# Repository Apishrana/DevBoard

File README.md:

# ATmega328 USB-C Devboard

Custom ATmega328-P based devboard for Arduino-like systems.

## Images

### Front

### Back

### PCB

### Schematic

---

## Features

- ATmega328-P as Microcontroller
- USB-C Support
- CH340G for USB-to-Serial
- Digital Pin `0-13`
- Analog Pin `A0-A5`
- 5 V VIN Regulation with L7805
- Reset Button

---

## Repository Structure

```text
.
├── BOM.csv
├── Devboard.kicad_pcb
├── Devboard.kicad_prl
├── Devboard.kicad_pro
├── Devboard.kicad_sch
├── grbr
│   ├── Devboard-B_Cu.gbl
│   ├── Devboard-B_Mask.gbs
│   ├── Devboard-B_Paste.gbp
│   ├── Devboard-B_Silkscreen.gbo
│   ├── Devboard-Edge_Cuts.gm1
│   ├── Devboard-F_Cu.gtl
│   ├── Devboard-F_Mask.gts
│   ├── Devboard-F_Paste.gtp
│   ├── Devboard-F_Silkscreen.gto
│   ├── Devboard-job.gbrjob
│   ├── Devboard-NPTH.drl
│   ├── Devboard-PTH.drl
│   └── Devboard.zip
├── image
│   ├── back.png
│   ├── front.png
│   ├── pcb.png
│   └── schema.png
└── README.md

3 directories, 23 files
```

---

## Board Details

- Microcontroller: `ATmega328-P`
- USB Serial: `CH340G`
- Main Clock: `16 MHz`
- USB Serial Clock: `12 MHz`
- Input Power: USB-C or `VIN`

`VIN`: `7-12 V`

---

## Author

Created by [Apish Rana](https://github.com/Apishrana)

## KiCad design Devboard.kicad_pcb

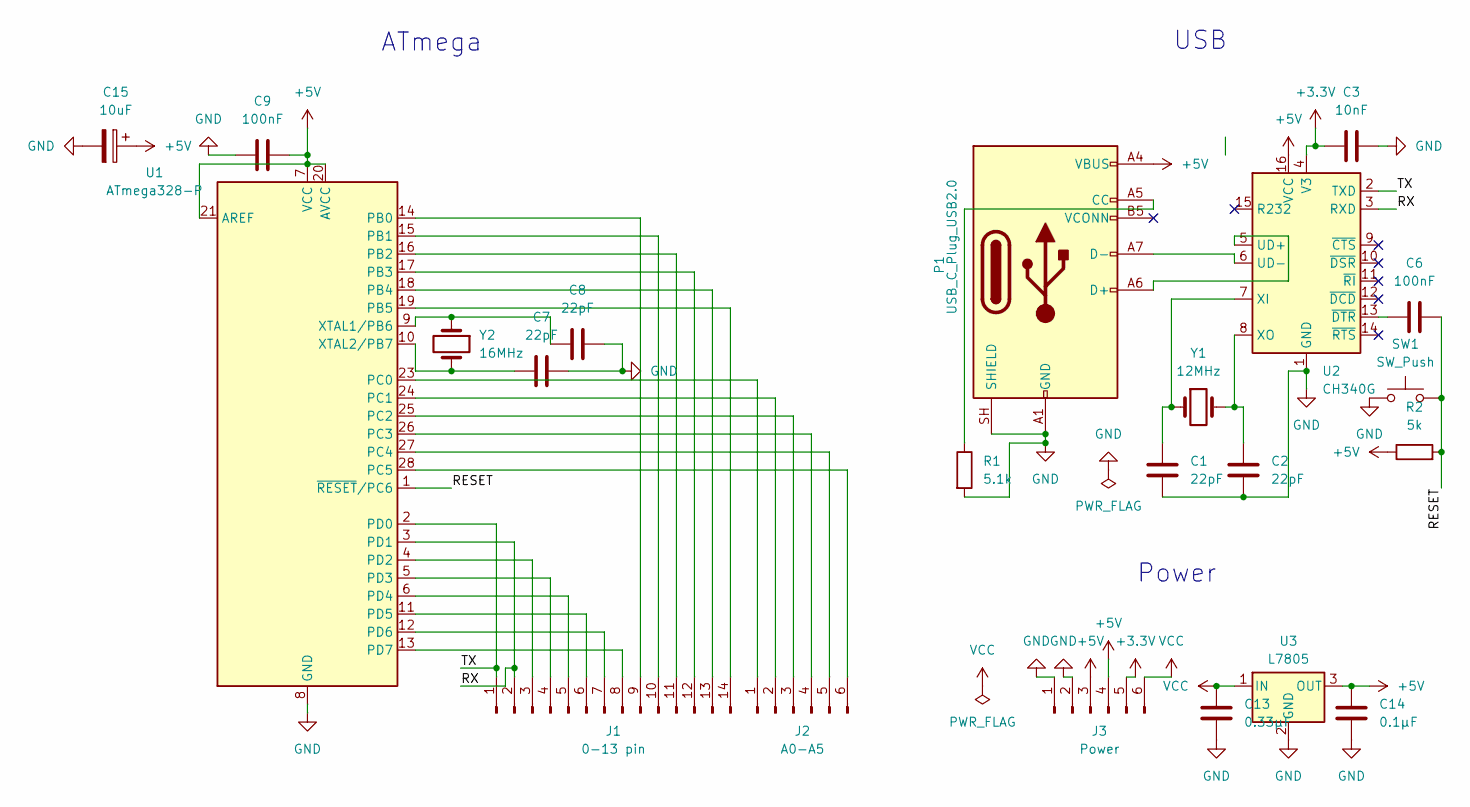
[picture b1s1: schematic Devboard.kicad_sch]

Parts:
C1, C2, C7, C8: 22pF; C_Disc_D5.0mm_W2.5mm_P5.00mm
C3: 10nF; C_Disc_D5.0mm_W2.5mm_P5.00mm
C6, C9: 100nF; C_Disc_D5.0mm_W2.5mm_P5.00mm
C13: 0.33µF; C_Disc_D5.0mm_W2.5mm_P5.00mm
C14: 0.1µF; C_Disc_D5.0mm_W2.5mm_P5.00mm
C15: 10uF; CP_Radial_D5.0mm_P2.00mm
J1: 0-13 pin; PinHeader_1x14_P2.54mm_Vertical
J2: A0-A5; PinHeader_1x06_P2.54mm_Vertical
J3: Power; PinHeader_1x06_P2.54mm_Vertical
P1: USB_C_Plug_USB2.0; USB_C_Receptacle_HRO_TYPE-C-31-M-12
R1: 5.1k; R_Axial_DIN0207_L6.3mm_D2.5mm_P7.62mm_Horizontal
R2: 5k; R_Axial_DIN0207_L6.3mm_D2.5mm_P7.62mm_Horizontal
SW1: SW_Push; SW_PUSH_6mm_H5mm
U1: ATmega328-P; DIP-28_W7.62mm
U2: CH340G; SOIC-16_3.9x9.9mm_P1.27mm
U3: L7805; TO-220-3_Vertical
Y1: 12MHz; Crystal_HC49-U_Vertical
Y2: 16MHz; Crystal_HC49-U_Vertical

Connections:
+3.3V: C3.1, J3.5, U2.4 (V3)
+5V: C9.1, C14.1, C15.1, J3.3, J3.4, P1.A4 (VBUS), P1.A9 (VBUS), P1.B4 (VBUS), P1.B9 (VBUS), R2.1, U1.7 (VCC), U1.20 (AVCC), U1.21 (AREF), U2.16 (VCC), U3.3 (OUT)
/RESET: C6.1, R2.2, SW1.2, U1.1 (~RESET/PC6)
/RX: J1.2, U1.3 (PD1), U2.3 (RXD)
/TX: J1.1, U1.2 (PD0), U2.2 (TXD)
GND: C1.2, C2.2, C3.2, C7.2, C8.2, C9.2, C13.2, C14.2, C15.2, J3.1, J3.2, P1.A1 (GND), P1.A12 (GND), P1.B1 (GND), P1.B12 (GND), P1.SH (SHIELD), R1.2, SW1.1, U1.8 (GND), U1.22 (GND), U2.1 (GND), U3.2 (GND)
unnamed: J1.3, U1.4 (PD2)
unnamed: J1.4, U1.5 (PD3)
unnamed: J1.5, U1.6 (PD4)
unnamed: J1.6, U1.11 (PD5)
unnamed: J1.7, U1.12 (PD6)
unnamed: J1.8, U1.13 (PD7)
unnamed: J1.9, U1.14 (PB0)
unnamed: J1.10, U1.15 (PB1)
unnamed: J1.11, U1.16 (PB2)
unnamed: J1.12, U1.17 (PB3)
unnamed: J1.13, U1.18 (PB4)
unnamed: J1.14, U1.19 (PB5)
unnamed: J2.1, U1.23 (PC0)
unnamed: J2.2, U1.24 (PC1)
unnamed: J2.3, U1.25 (PC2)
unnamed: J2.4, U1.26 (PC3)
unnamed: J2.5, U1.27 (PC4)
unnamed: J2.6, U1.28 (PC5)
unnamed: P1.A5 (CC), R1.1
unnamed: P1.A6 (D+), U2.5 (UD+)
unnamed: P1.A7 (D-), U2.6 (UD-)
unnamed: C8.1, U1.9 (XTAL1/PB6), Y2.1
unnamed: C7.1, U1.10 (XTAL2/PB7), Y2.2
unnamed: C1.1, U2.7 (XI), Y1.1
unnamed: C2.1, U2.8 (XO), Y1.2
unnamed: C6.2, U2.13 (~DTR)
VCC: C13.1, J3.6, U3.1 (IN)

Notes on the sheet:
USB
Power
ATmega

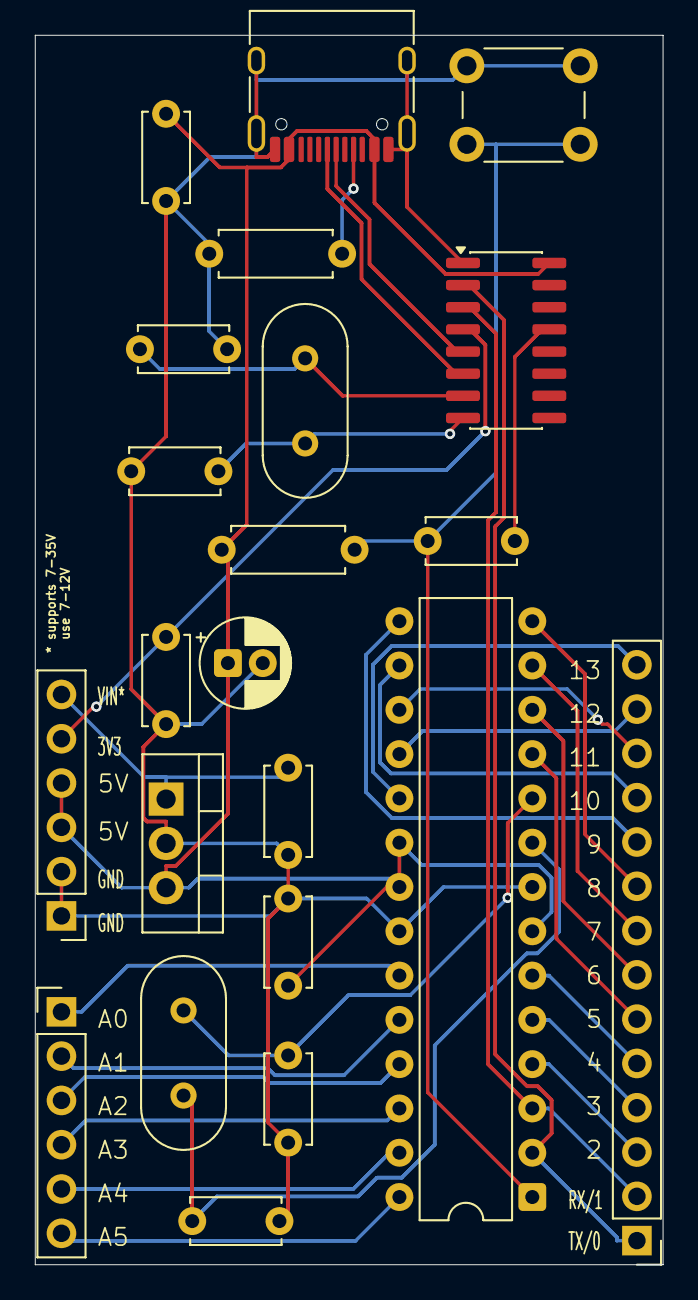
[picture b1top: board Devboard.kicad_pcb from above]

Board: 2 copper layers, 36.0 x 70.5 mm, 22 parts (0 on the bottom side), 33 nets.

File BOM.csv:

"Reference","Qty","Value"
"C1,C2,C7,C8","4","22pF"
"C3","1","10nF"
"C6,C9","2","100nF"
"C13","1","0.33µF"
"C14","1","0.1µF"
"C15","1","10uF"
"J1","1","0-13 pin"
"J2","1","A0-A5"
"J3","1","Power"
"P1","1","USB_C_Plug_USB2.0"
"R1","1","5.1k"
"R2","1","5k"
"SW1","1","SW_Push"
"U1","1","ATmega328-P"
"U2","1","CH340G"
"U3","1","L7805"
"Y1","1","12MHz"
"Y2","1","16MHz"

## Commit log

2026-05-17 Schematic
2026-05-19 Added pcb lbeling
2026-05-22 final dessine
2026-05-22 readme
